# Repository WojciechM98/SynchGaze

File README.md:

# SynchGaze
A project that allows you to control camera movement by moving your head.

## Project assumptions
The project includes two boards SynchGaze Transmiter and SynchGaze Motor Control that communicate with each other via bluetooth.

## SynchGaze Transmiter
Transmiter board has IMU device to collect position, acceleration and rotation data. Every information is preprocessed and send in real time by ESP32 to Motor Control board.
This board should be neatly attached to the user's head.

## SynchGaze Motor Control
Motor Control board recieve preprocessed data from Transmiter and converts it into BLDC motors movement. STM32 works in closed loop gathering data from external IMU device whith is attached in the same place as camera. When new information from Transmiter board is recieved the possition according to external IMU is corrected by sending information about revolutions and acceleration to specific motor controler.

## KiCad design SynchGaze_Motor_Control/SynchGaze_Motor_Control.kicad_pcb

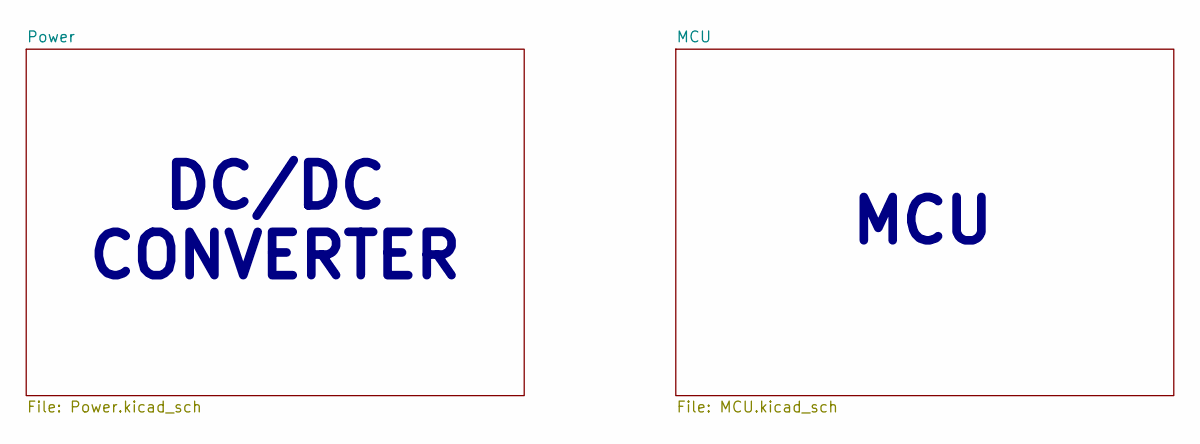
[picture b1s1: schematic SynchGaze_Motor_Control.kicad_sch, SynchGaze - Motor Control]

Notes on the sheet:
DC/DC CONVERTER
MCU

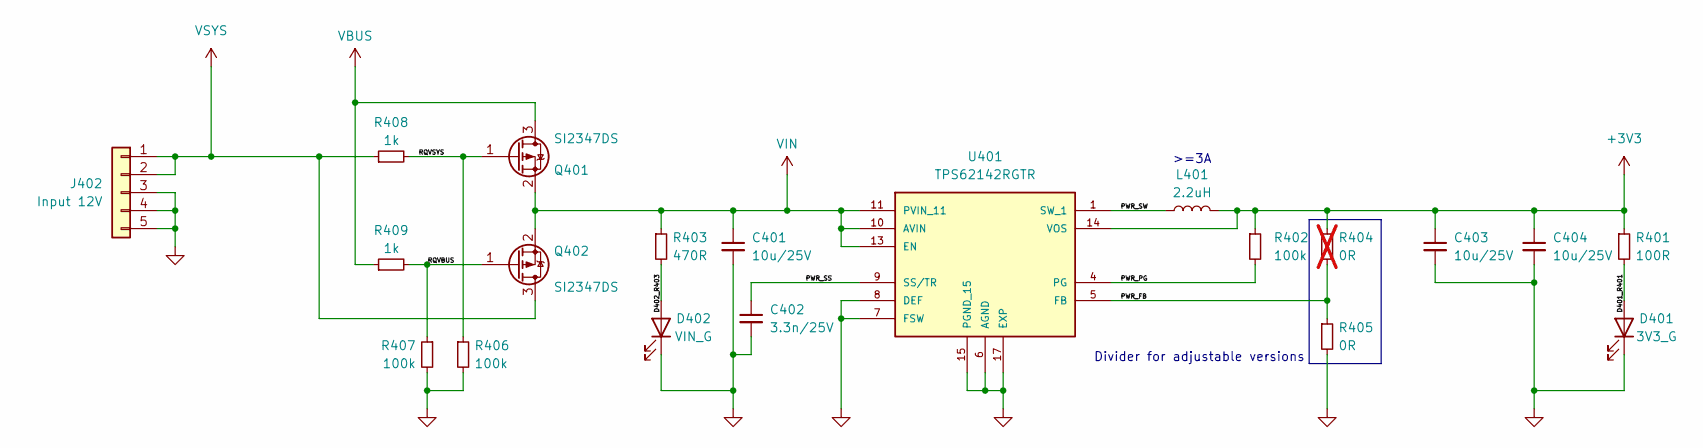
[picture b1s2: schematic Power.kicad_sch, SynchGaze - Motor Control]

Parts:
C401, C403, C404: 10u/25V; C_1206_3216Metric; Manufacturer Part Number CL31B106KAHNFNE
C402: 3.3n/25V; C_0402_1005Metric; Manufacturer Part Number 885012205047
D401: 3V3_G; LED_0603_1608Metric; Manufacturer Part Number 150060GS55040
D402: VIN_G; LED_0603_1608Metric; Manufacturer Part Number 150060GS55040
J402: Input 12V; CONN5_B05B-XASK-1-A_JST
L401: 2.2uH; IHLP1212BZEV2R2MA1; Manufacturer Part Number IHLP1212BZEV2R2MA1
Q401, Q402: SI2347DS; TSOT-23
R401: 100R; R_0402_1005Metric; Manufacturer Part Number RC0402JR-07100RP
R402, R406, R407: 100k; R_0402_1005Metric; Manufacturer Part Number WR04X104 JTL
R403: 470R; R_0402_1005Metric; Manufacturer Part Number RT0402FRE07470RL
R404: 0R; R_0402_1005Metric; Manufacturer Part Number RC0402JR-07100RP; not fitted
R405: 0R; R_0402_1005Metric; Manufacturer Part Number RC0402JR-070RP
R408, R409: 1k; R_0402_1005Metric; Manufacturer Part Number RT0402FRE07470RL
U401: TPS62142RGTR; QFN50P300X300X100-17N_TPS62142RGTR; PARTREV E

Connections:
+3V3: C403.1, C404.1, L401.2, R401.1, R402.1, R404.1, U401.14 (VOS); also elsewhere on the board
/Power/D401_R401: D401.2 (A), R401.2
/Power/D402_R403: D402.2 (A), R403.2
/Power/PWR_FB: R404.2, R405.1, U401.5 (FB)
/Power/PWR_PG: R402.2, U401.4 (PG)
/Power/PWR_SS: C402.1, U401.9 (SS/TR)
/Power/PWR_SW: L401.1, U401.1 (SW_1), U401.2 (SW_2), U401.3 (SW_3)
/Power/RQVBUS: Q402.1 (G), R407.1, R409.2
/Power/RQVSYS: Q401.1 (G), R406.1, R408.2
GND: C401.2, C402.2, C403.2, C404.2, D401.1 (K), D402.1 (K), J402.3, J402.4, J402.5, R405.2, R406.2, R407.2, U401.6 (AGND), U401.7 (FSW), U401.8 (DEF), U401.15 (PGND_15), U401.16 (PGND_16), U401.17 (EXP); also elsewhere on the board
VBUS: Q401.3 (D), R409.1; also elsewhere on the board
VIN: C401.1, Q401.2 (S), Q402.2 (S), R403.1, U401.10 (AVIN), U401.11 (PVIN_11), U401.12 (PVIN_12), U401.13 (EN)
VSYS: J402.1, J402.2, Q402.3 (D), R408.1; also elsewhere on the board

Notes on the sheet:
Divider for adjustable versions
>=3A

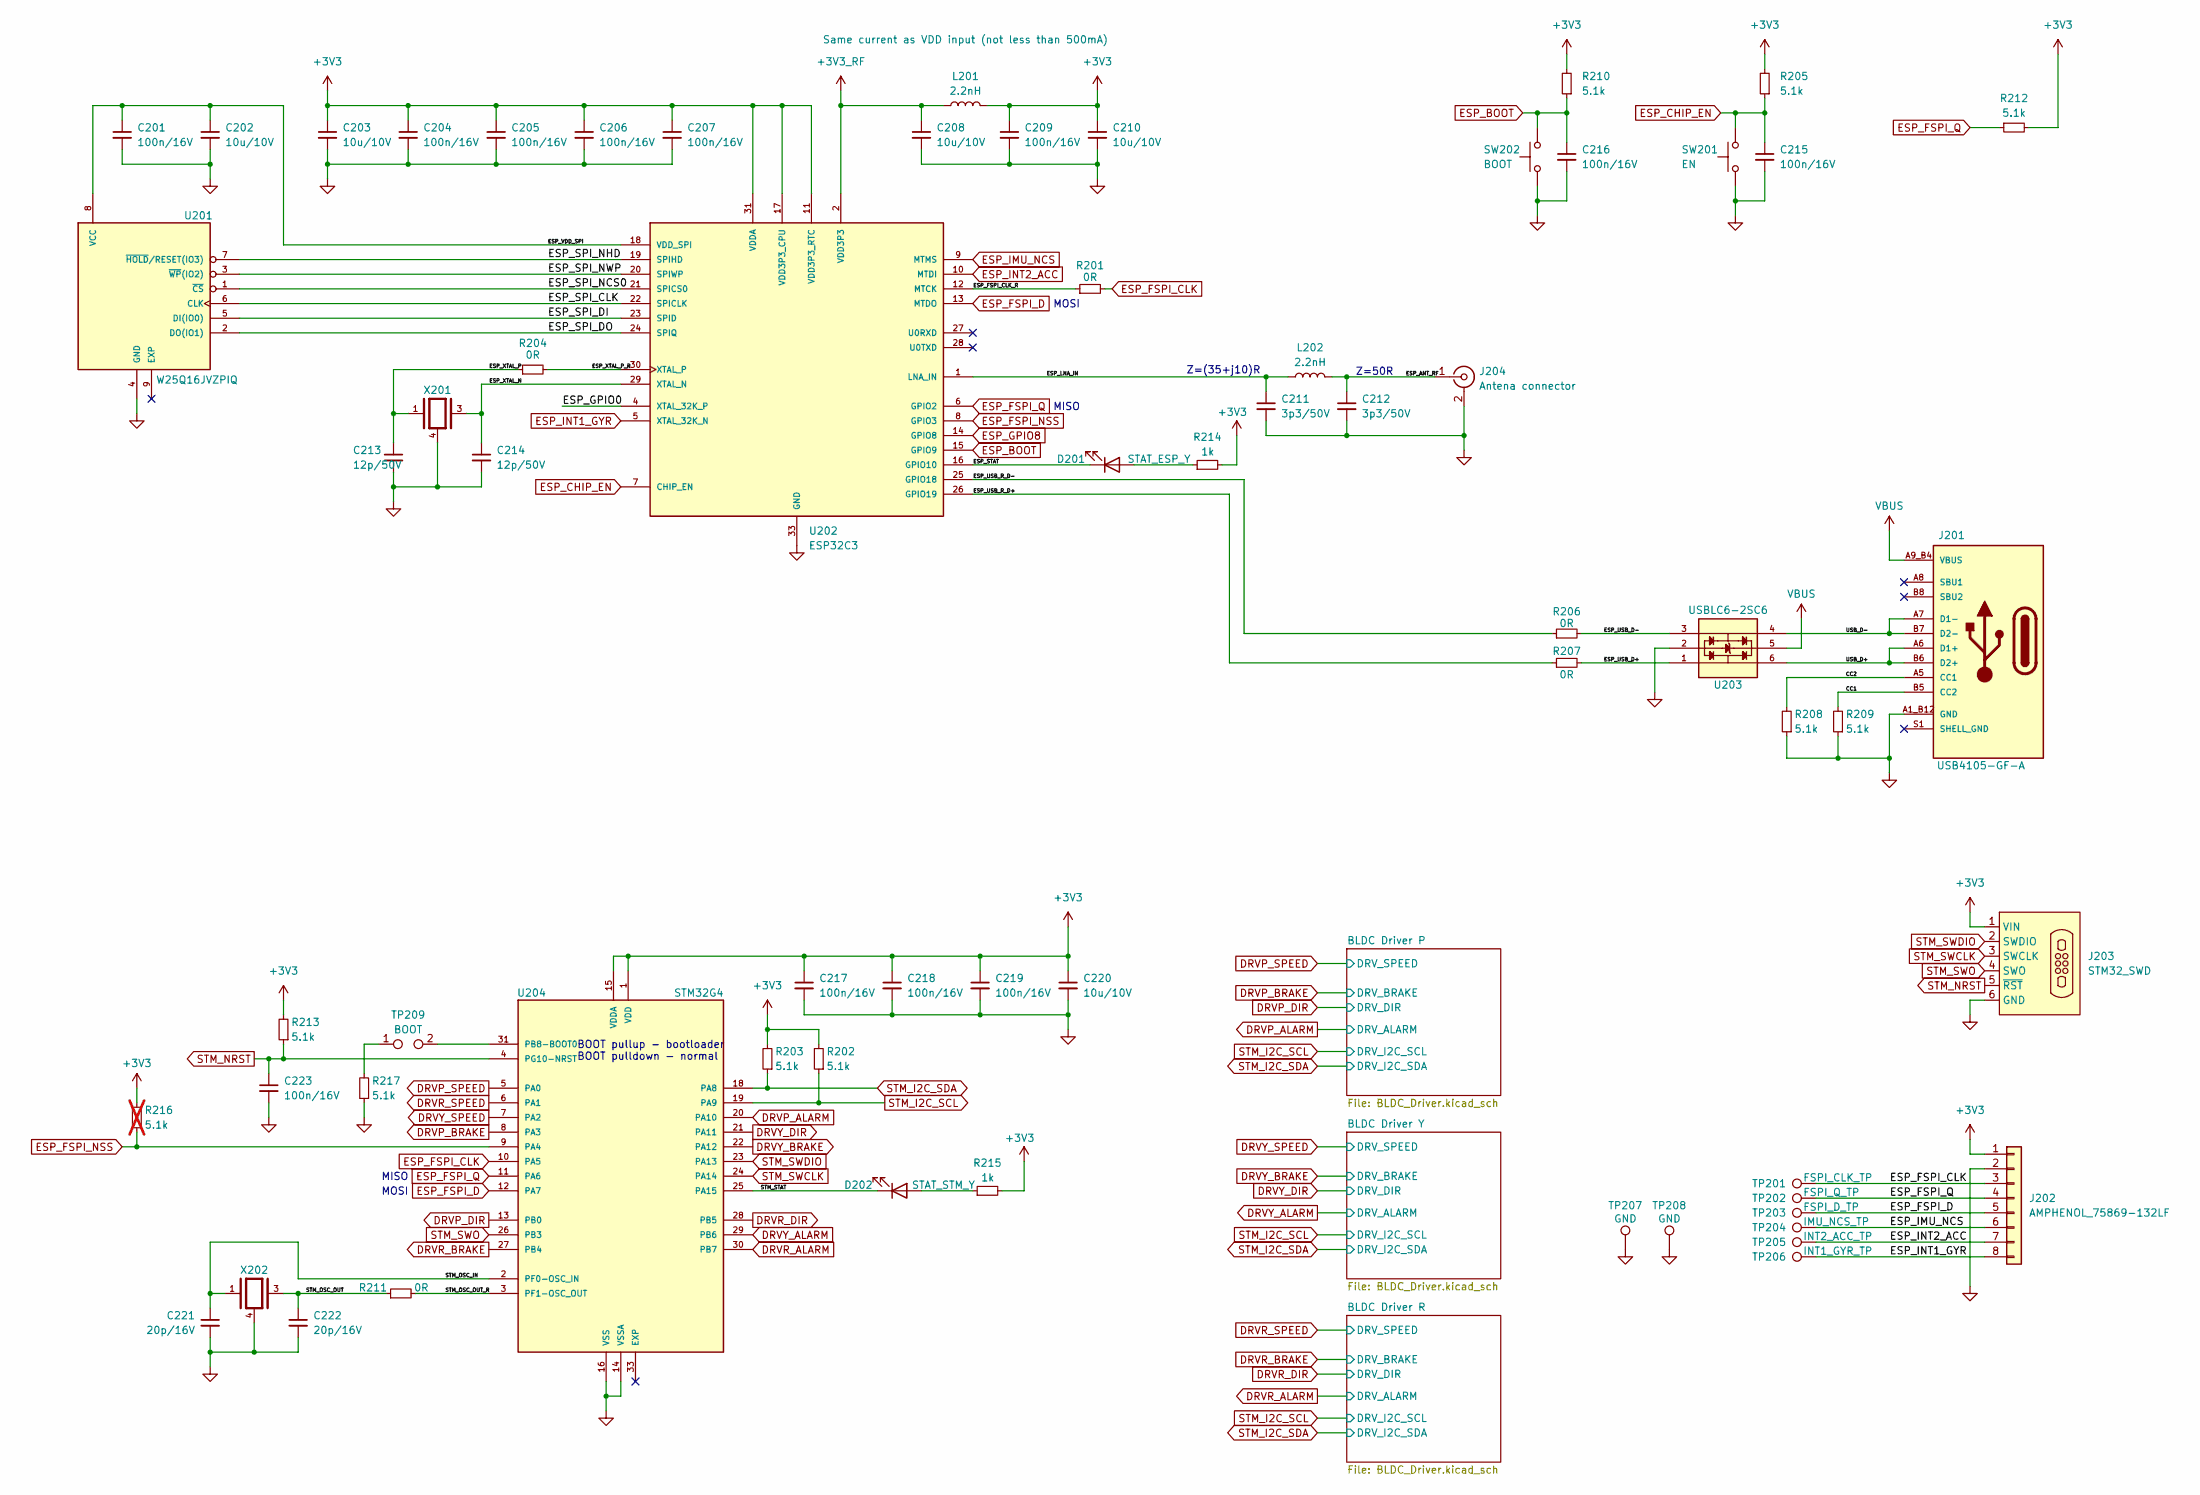
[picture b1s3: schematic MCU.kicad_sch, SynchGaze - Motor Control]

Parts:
C201, C204, C205, C206, C207, C209, C215, C216, C217, C218, C219, C223: 100n/16V; C_0402_1005Metric; Manufacturer Part Number CL05B104JO5NNNC
C202, C203, C208, C210, C220: 10u/10V; C_0402_1005Metric; Manufacturer Part Number GRM155R61A106ME11J
C211, C212: 3p3/50V; C_0402_1005Metric; Manufacturer Part Number 0402N3R3D500CT
C213, C214: 12p/50V; C_0402_1005Metric; Manufacturer Part Number GRM1555C1H120JA01D
C221, C222: 20p/16V; C_0402_1005Metric; Manufacturer Part Number 0402N200J160CT
D201: STAT_ESP_Y; LED_0603_1608Metric; Manufacturer Part Number 150060YS55040
D202: STAT_STM_Y; LED_0603_1608Metric; Manufacturer Part Number 150060YS55040
J201: USB4105-GF-A; GCT_USB4105-GF-A; PARTREV 3
J202: AMPHENOL_75869-132LF; Manufacturer Part Number 0530470810
J203: STM32_SWD; PogoConnector
J204: Antena connector; LINX_CONMHF1-SMD-G-T
L201, L202: 2.2nH; L_0402_1005Metric; Manufacturer Part Number LQG15HN2N2S02D
R201, R204, R206, R207, R211: 0R; R_0402_1005Metric; Manufacturer Part Number RC0402JR-070RP
R202, R203, R205, R208, R209, R210, R212, R213, R217: 5.1k; R_0402_1005Metric; Manufacturer Part Number RT0402FRE075K1L
R214, R215: 1k; R_0402_1005Metric; Manufacturer Part Number RT0402FRE07470RL
R216: 5.1k; R_0402_1005Metric; Manufacturer Part Number RT0402FRE075K1L; not fitted
SW201: EN; SW4_PTS815 SJM 250 SMTR LFS_CNK; Manufacturer Part Number RKB2SJM250SMTR LFS
SW202: BOOT; SW4_PTS815 SJM 250 SMTR LFS_CNK; Manufacturer Part Number RKB2SJM250SMTR LFS
TP201: FSPI_CLK_TP; test_point_SMD_0.5mm
TP202: FSPI_Q_TP; test_point_SMD_0.5mm
TP203: FSPI_D_TP; test_point_SMD_0.5mm
TP204: IMU_NCS_TP; test_point_SMD_0.5mm
TP205: INT2_ACC_TP; test_point_SMD_0.5mm
TP206: INT1_GYR_TP; test_point_SMD_0.5mm
TP207, TP208: GND; test_point_THT 0.7mm
TP209: BOOT; test_point_SMD_two_pad_1mm
U201: W25Q16JVZPIQ; SON127P500X600X80-9N; Manufacturer Part Number W25Q16JVZPIQ
U202: ESP32C3; QFN32_5X5MM_ESP32C3; Manufacturer Part Number ESP32-C3
U203: USBLC6-2SC6; SOT95P280X145-6N; Manufacturer Part Number USBLC6-2SC6
U204: STM32G4; QFN50P500X500X60-33N_STM32G431KBU3; PARTREV 4
X201: XRCGB40M000F4M02R0; OSC_XRCGB40M000F4M02R0; PARTREV N/A
X202: 830108208209; Crystal_SMD_2520-4Pin_2.5x2.0mm; Manufacturer Part Number 830108208209

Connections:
+3V3: C203.1, C204.1, C205.1, C206.1, C207.1, C209.1, C210.1, C217.1, C218.1, C219.1, C220.1, J202.1, J203.1 (VIN), L201.2, R202.2, R203.2, R205.2, R210.2, R212.2, R213.2, R214.2, R215.2, R216.2, U202.11 (VDD3P3_RTC), U202.17 (VDD3P3_CPU), U202.31 (VDDA), U202.32 (VDDA), U204.1 (VDD), U204.15 (VDDA), U204.17 (VDD); also elsewhere on the board
+3V3_RF: C208.1, L201.1, U202.2 (VDD3P3), U202.3 (VDD3P3)
/MCU/CC1: J201.B5 (CC2), R209.2
/MCU/CC2: J201.A5 (CC1), R208.2
/MCU/ESP_ANT_RF: C212.1, J204.1 (In), L202.2
/MCU/ESP_FSPI_CLK_R: R201.1, U202.12 (MTCK)
/MCU/ESP_GPIO0: U202.4 (XTAL_32K_P)
/MCU/ESP_LNA_IN: C211.1, L202.1, U202.1 (LNA_IN)
/MCU/ESP_SPI_CLK: U201.6 (CLK), U202.22 (SPICLK)
/MCU/ESP_SPI_DI: U201.5 (DI(IO0)), U202.23 (SPID)
/MCU/ESP_SPI_DO: U201.2 (DO(IO1)), U202.24 (SPIQ)
/MCU/ESP_SPI_NCS0: U201.1 (~CS), U202.21 (SPICS0)
/MCU/ESP_SPI_NHD: U201.7 (~HOLD/RESET(IO3)), U202.19 (SPIHD)
/MCU/ESP_SPI_NWP: U201.3 (~WP(IO2)), U202.20 (SPIWP)
/MCU/ESP_STAT: D201.1 (K), U202.16 (GPIO10)
/MCU/ESP_USB_D+: R207.2, U203.1
/MCU/ESP_USB_D-: R206.2, U203.3
/MCU/ESP_USB_R_D+: R207.1, U202.26 (GPIO19)
/MCU/ESP_USB_R_D-: R206.1, U202.25 (GPIO18)
/MCU/ESP_VDD_SPI: C201.1, C202.1, U201.8 (VCC), U202.18 (VDD_SPI)
/MCU/ESP_XTAL_N: C214.1, U202.29 (XTAL_N), X201.3
/MCU/ESP_XTAL_P: C213.1, R204.1, X201.1
/MCU/ESP_XTAL_P_R: R204.2, U202.30 (XTAL_P)
/MCU/STM_OSC_IN: C221.1, U204.2 (PF0-OSC_IN), X202.1
/MCU/STM_OSC_OUT: C222.1, R211.1, X202.3
/MCU/STM_OSC_OUT_R: R211.2, U204.3 (PF1-OSC_OUT)
/MCU/STM_STAT: D202.1 (K), U204.25 (PA15)
/MCU/USB_D+: J201.A6 (D1+), J201.B6 (D2+), U203.6
/MCU/USB_D-: J201.A7 (D1-), J201.B7 (D2-), U203.4
DRVP_ALARM: U204.20 (PA10); also elsewhere on the board
DRVP_BRAKE: U204.8 (PA3); also elsewhere on the board
DRVP_DIR: U204.13 (PB0); also elsewhere on the board
DRVP_SPEED: U204.5 (PA0); also elsewhere on the board
DRVR_ALARM: U204.30 (PB7); also elsewhere on the board
DRVR_BRAKE: U204.27 (PB4); also elsewhere on the board
DRVR_DIR: U204.28 (PB5); also elsewhere on the board
DRVR_SPEED: U204.6 (PA1); also elsewhere on the board
DRVY_ALARM: U204.29 (PB6); also elsewhere on the board
DRVY_BRAKE: U204.22 (PA12); also elsewhere on the board
DRVY_DIR: U204.21 (PA11); also elsewhere on the board
DRVY_SPEED: U204.7 (PA2); also elsewhere on the board
ESP_BOOT: C216.1, R210.1, SW202.2, U202.15 (GPIO9)
ESP_CHIP_EN: C215.1, R205.1, SW201.2, U202.7 (CHIP_EN)
ESP_FSPI_CLK: J202.3, R201.2, TP201.1, U204.10 (PA5)
ESP_FSPI_D: J202.5, TP203.1, U202.13 (MTDO), U204.12 (PA7)
ESP_FSPI_NSS: R216.1, U202.8 (GPIO3), U204.9 (PA4)
ESP_FSPI_Q: J202.4, R212.1, TP202.1, U202.6 (GPIO2), U204.11 (PA6)
ESP_GPIO8: U202.14 (GPIO8)
ESP_IMU_NCS: J202.6, TP204.1, U202.9 (MTMS)
ESP_INT1_GYR: J202.8, TP206.1, U202.5 (XTAL_32K_N)
ESP_INT2_ACC: J202.7, TP205.1, U202.10 (MTDI)
GND: C201.2, C202.2, C203.2, C204.2, C205.2, C206.2, C207.2, C208.2, C209.2, C210.2, C211.2, C212.2, C213.2, C214.2, C215.2, C216.2, C217.2, C218.2, C219.2, C220.2, C221.2, C222.2, C223.2, J201.A1_B12 (GND), J201.A12_B1 (GND), J202.2, J203.6 (GND), J204.2 (Ext), R208.1, R209.1, R217.1, SW201.1, SW202.1, TP207.1, TP208.1, U201.4 (GND), U202.33 (GND), U203.2, U204.14 (VSSA), U204.16 (VSS), U204.32 (VSS), X201.2, X201.4, X202.2, X202.4; also elsewhere on the board
unnamed: D201.2 (A), R214.1
unnamed: D202.2 (A), R215.1
unnamed: R217.2, TP209.1
unnamed: TP209.2, U204.31 (PB8-BOOT0)
STM_I2C_SCL: R202.1, U204.19 (PA9); also elsewhere on the board
STM_I2C_SDA: R203.1, U204.18 (PA8); also elsewhere on the board
STM_NRST: C223.1, J203.5 (~RST), R213.1, U204.4 (PG10-NRST)
STM_SWCLK: J203.3 (SWCLK), U204.24 (PA14)
STM_SWDIO: J203.2 (SWDIO), U204.23 (PA13)
STM_SWO: J203.4 (SWO), U204.26 (PB3)
VBUS: J201.A4_B9 (VBUS), J201.A9_B4 (VBUS), U203.5; also elsewhere on the board

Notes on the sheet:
MOSI
Z=(35+j10)R
BOOT pullup - bootloader BOOT pulldown - normal
MISO
Z=50R

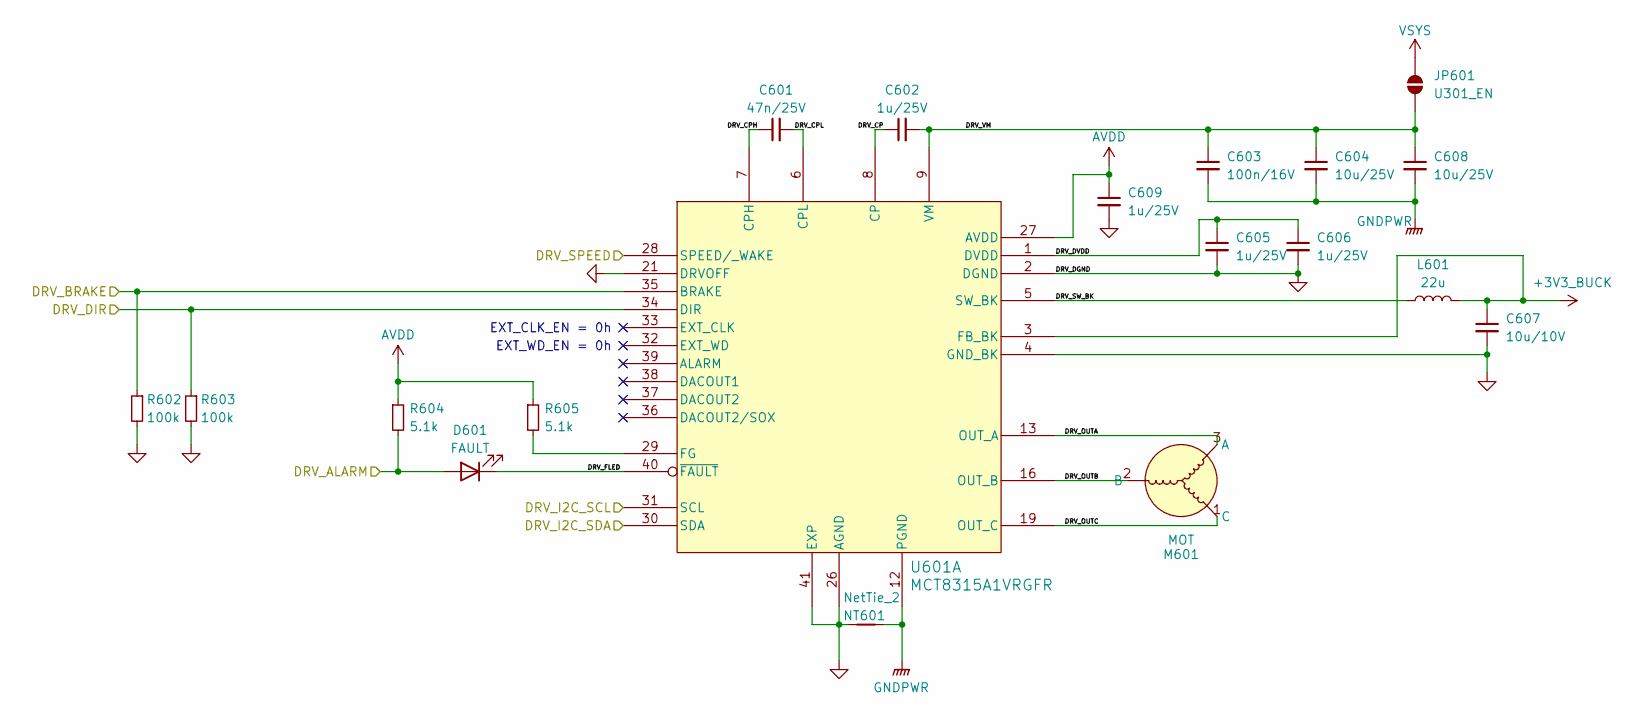
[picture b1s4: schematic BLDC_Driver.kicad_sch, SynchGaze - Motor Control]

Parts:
C601: 47n/25V; C_0402_1005Metric; Manufacturer Part Number GRT155R71E473KE01D
C602, C605, C606, C609: 1u/25V; C_0402_1005Metric; Manufacturer Part Number GRM155R61E105KA12J
C603: 100n/16V; C_0402_1005Metric; Manufacturer Part Number CL05B104JO5NNNC
C604, C608: 10u/25V; C_1206_3216Metric; Manufacturer Part Number CL31B106KAHNFNE
C607: 10u/10V; C_0402_1005Metric; Manufacturer Part Number GRM155R61A106ME11J
D601: FAULT; LED_0603_1608Metric; Manufacturer Part Number SML-D12U1WT86
JP601: U301_EN; SolderJumper-2_P1.3mm_Open_RoundedPad1.0x1.5mm
L601: 22u; L_1210_3225Metric; Manufacturer Part Number CBC3225T220MR
M601: MOT; 15EDGVC-3-5-03P
NT601: NetTie_2; NetTie_2_0.4mm
R602, R603: 100k; R_0402_1005Metric; Manufacturer Part Number WR04X104 JTL
R604, R605: 5.1k; R_0402_1005Metric; Manufacturer Part Number RT0402FRE075K1L
U601: MCT8315A1VRGFR; VQFN40_RGF_TEX_MCT8315A1VRGFR; Manufacturer Part Number MCT8315A1VRGFR

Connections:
+3V3_BUCK: C607.1, L601.2, U601.3 (FB_BK); also elsewhere on the board
/MCU/BLDC Driver R/DRV_CP: C602.1, U601.8 (CP)
/MCU/BLDC Driver R/DRV_CPH: C601.1, U601.7 (CPH)
/MCU/BLDC Driver R/DRV_CPL: C601.2, U601.6 (CPL)
/MCU/BLDC Driver R/DRV_DVDD: C605.1, C606.1, U601.1 (DVDD)
/MCU/BLDC Driver R/DRV_FLED: D601.1 (K), U601.40 (~FAULT)
/MCU/BLDC Driver R/DRV_OUTA: M601.3 (A), U601.13 (OUT_A), U601.14 (OUT_A)
/MCU/BLDC Driver R/DRV_OUTB: M601.2 (B), U601.16 (OUT_B), U601.17 (OUT_B)
/MCU/BLDC Driver R/DRV_OUTC: M601.1 (C), U601.19 (OUT_C), U601.20 (OUT_C)
/MCU/BLDC Driver R/DRV_SW_BK: L601.1, U601.5 (SW_BK)
AVDD: C609.1, R604.1, R605.1, U601.27 (AVDD); also elsewhere on the board
DRVR_ALARM: D601.2 (A), R604.2; also elsewhere on the board
DRVR_BRAKE: R602.1, U601.35 (BRAKE); also elsewhere on the board
DRVR_DIR: R603.1, U601.34 (DIR); also elsewhere on the board
DRVR_SPEED: U601.28 (SPEED/_WAKE); also elsewhere on the board
GND: C605.2, C606.2, C607.2, C609.2, NT601.2, R602.2, R603.2, U601.2 (DGND), U601.4 (GND_BK), U601.21 (DRVOFF), U601.26 (AGND), U601.41 (EXP); also elsewhere on the board
GNDPWR: C603.2, C604.2, C608.2, NT601.1, U601.12 (PGND), U601.15 (PGND), U601.18 (PGND); also elsewhere on the board
unnamed: R605.2, U601.29 (FG)
STM_I2C_SCL: U601.31 (SCL); also elsewhere on the board
STM_I2C_SDA: U601.30 (SDA); also elsewhere on the board
VM: C602.2, C603.1, C604.1, C608.1, JP601.1 (A), U601.9 (VM), U601.10 (VM), U601.11 (VM); also elsewhere on the board
VSYS: JP601.2 (B); also elsewhere on the board

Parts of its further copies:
C301, C501: 47n/25V; C_0402_1005Metric; Manufacturer Part Number GRT155R71E473KE01D
C302, C305, C306, C309, C502, C506, C507, C509: 1u/25V; C_0402_1005Metric; Manufacturer Part Number GRM155R61E105KA12J
C303, C503: 100n/16V; C_0402_1005Metric; Manufacturer Part Number CL05B104JO5NNNC
C304, C308, C504, C505: 10u/25V; C_1206_3216Metric; Manufacturer Part Number CL31B106KAHNFNE
C307, C508: 10u/10V; C_0402_1005Metric; Manufacturer Part Number GRM155R61A106ME11J
D301, D501: FAULT; LED_0603_1608Metric; Manufacturer Part Number SML-D12U1WT86
JP301, JP501: U301_EN; SolderJumper-2_P1.3mm_Open_RoundedPad1.0x1.5mm
L301, L501: 22u; L_1210_3225Metric; Manufacturer Part Number CBC3225T220MR
M301, M501: MOT; 15EDGVC-3-5-03P
NT301, NT501: NetTie_2; NetTie_2_0.4mm
R302, R303, R502, R503: 100k; R_0402_1005Metric; Manufacturer Part Number WR04X104 JTL
R304, R305, R504, R505: 5.1k; R_0402_1005Metric; Manufacturer Part Number RT0402FRE075K1L
U301, U501: MCT8315A1VRGFR; VQFN40_RGF_TEX_MCT8315A1VRGFR; Manufacturer Part Number MCT8315A1VRGFR

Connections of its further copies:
+3V3_BUCK: C307.1, C508.1, L301.2, L501.2, U301.3 (FB_BK), U501.3 (FB_BK); also elsewhere on the board
/MCU/BLDC Driver P/DRV_CP: C502.1, U501.8 (CP)
/MCU/BLDC Driver P/DRV_CPH: C501.1, U501.7 (CPH)
/MCU/BLDC Driver P/DRV_CPL: C501.2, U501.6 (CPL)
/MCU/BLDC Driver P/DRV_DVDD: C506.1, C507.1, U501.1 (DVDD)
/MCU/BLDC Driver P/DRV_FLED: D501.1 (K), U501.40 (~FAULT)
/MCU/BLDC Driver P/DRV_OUTA: M501.3 (A), U501.13 (OUT_A), U501.14 (OUT_A)
/MCU/BLDC Driver P/DRV_OUTB: M501.2 (B), U501.16 (OUT_B), U501.17 (OUT_B)
/MCU/BLDC Driver P/DRV_OUTC: M501.1 (C), U501.19 (OUT_C), U501.20 (OUT_C)
/MCU/BLDC Driver P/DRV_SW_BK: L501.1, U501.5 (SW_BK)
/MCU/BLDC Driver Y/DRV_CP: C302.1, U301.8 (CP)
/MCU/BLDC Driver Y/DRV_CPH: C301.1, U301.7 (CPH)
/MCU/BLDC Driver Y/DRV_CPL: C301.2, U301.6 (CPL)
/MCU/BLDC Driver Y/DRV_DVDD: C305.1, C306.1, U301.1 (DVDD)
/MCU/BLDC Driver Y/DRV_FLED: D301.1 (K), U301.40 (~FAULT)
/MCU/BLDC Driver Y/DRV_OUTA: M301.3 (A), U301.13 (OUT_A), U301.14 (OUT_A)
/MCU/BLDC Driver Y/DRV_OUTB: M301.2 (B), U301.16 (OUT_B), U301.17 (OUT_B)
/MCU/BLDC Driver Y/DRV_OUTC: M301.1 (C), U301.19 (OUT_C), U301.20 (OUT_C)
/MCU/BLDC Driver Y/DRV_SW_BK: L301.1, U301.5 (SW_BK)
AVDD: C309.1, C509.1, R304.1, R305.1, R504.1, R505.1, U301.27 (AVDD), U501.27 (AVDD); also elsewhere on the board
DRVP_ALARM: D501.2 (A), R504.2; also elsewhere on the board
DRVP_BRAKE: R502.1, U501.35 (BRAKE); also elsewhere on the board
DRVP_DIR: R503.1, U501.34 (DIR); also elsewhere on the board
DRVP_SPEED: U501.28 (SPEED/_WAKE); also elsewhere on the board
DRVY_ALARM: D301.2 (A), R304.2; also elsewhere on the board
DRVY_BRAKE: R302.1, U301.35 (BRAKE); also elsewhere on the board
DRVY_DIR: R303.1, U301.34 (DIR); also elsewhere on the board
DRVY_SPEED: U301.28 (SPEED/_WAKE); also elsewhere on the board
GND: C305.2, C306.2, C307.2, C309.2, C506.2, C507.2, C508.2, C509.2, NT301.2, NT501.2, R302.2, R303.2, R502.2, R503.2, U301.2 (DGND), U301.4 (GND_BK), U301.21 (DRVOFF), U301.26 (AGND), U301.41 (EXP), U501.2 (DGND), U501.4 (GND_BK), U501.21 (DRVOFF), U501.26 (AGND), U501.41 (EXP); also elsewhere on the board
GNDPWR: C303.2, C304.2, C308.2, C503.2, C504.2, C505.2, NT301.1, NT501.1, U301.12 (PGND), U301.15 (PGND), U301.18 (PGND), U501.12 (PGND), U501.15 (PGND), U501.18 (PGND); also elsewhere on the board
unnamed: R305.2, U301.29 (FG)
unnamed: R505.2, U501.29 (FG)
STM_I2C_SCL: U301.31 (SCL), U501.31 (SCL); also elsewhere on the board
STM_I2C_SDA: U301.30 (SDA), U501.30 (SDA); also elsewhere on the board
VM: C302.2, C303.1, C304.1, C308.1, C502.2, C503.1, C504.1, C505.1, JP301.1 (A), JP501.1 (A), U301.9 (VM), U301.10 (VM), U301.11 (VM), U501.9 (VM), U501.10 (VM), U501.11 (VM); also elsewhere on the board
VSYS: JP301.2 (B), JP501.2 (B); also elsewhere on the board

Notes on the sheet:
EXT_CLK_EN = 0h
EXT_WD_EN = 0h

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
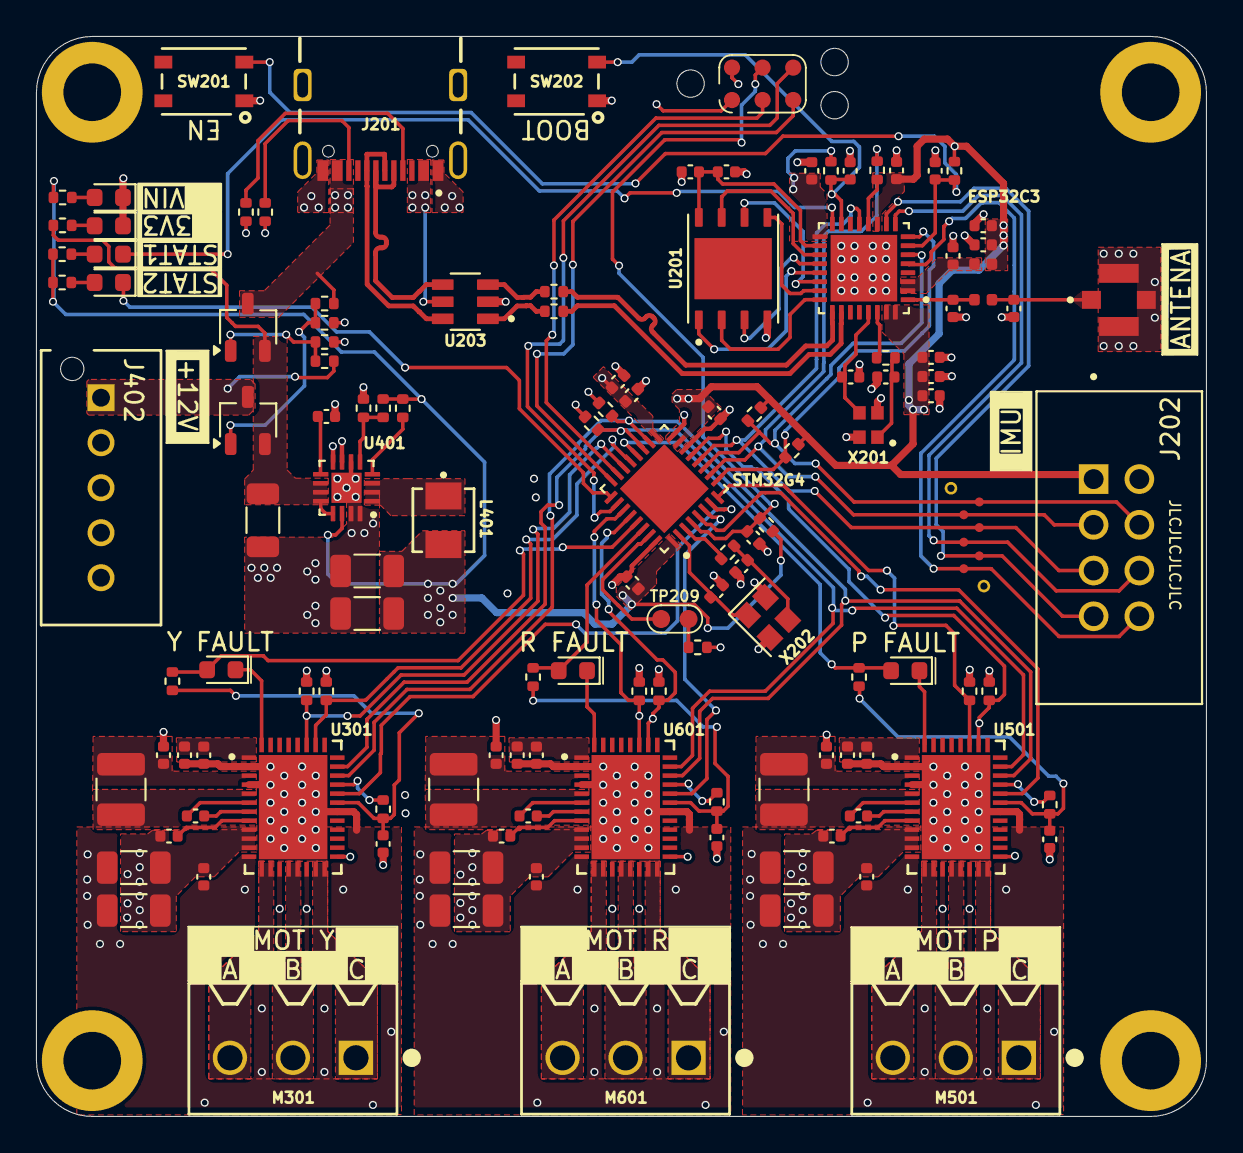
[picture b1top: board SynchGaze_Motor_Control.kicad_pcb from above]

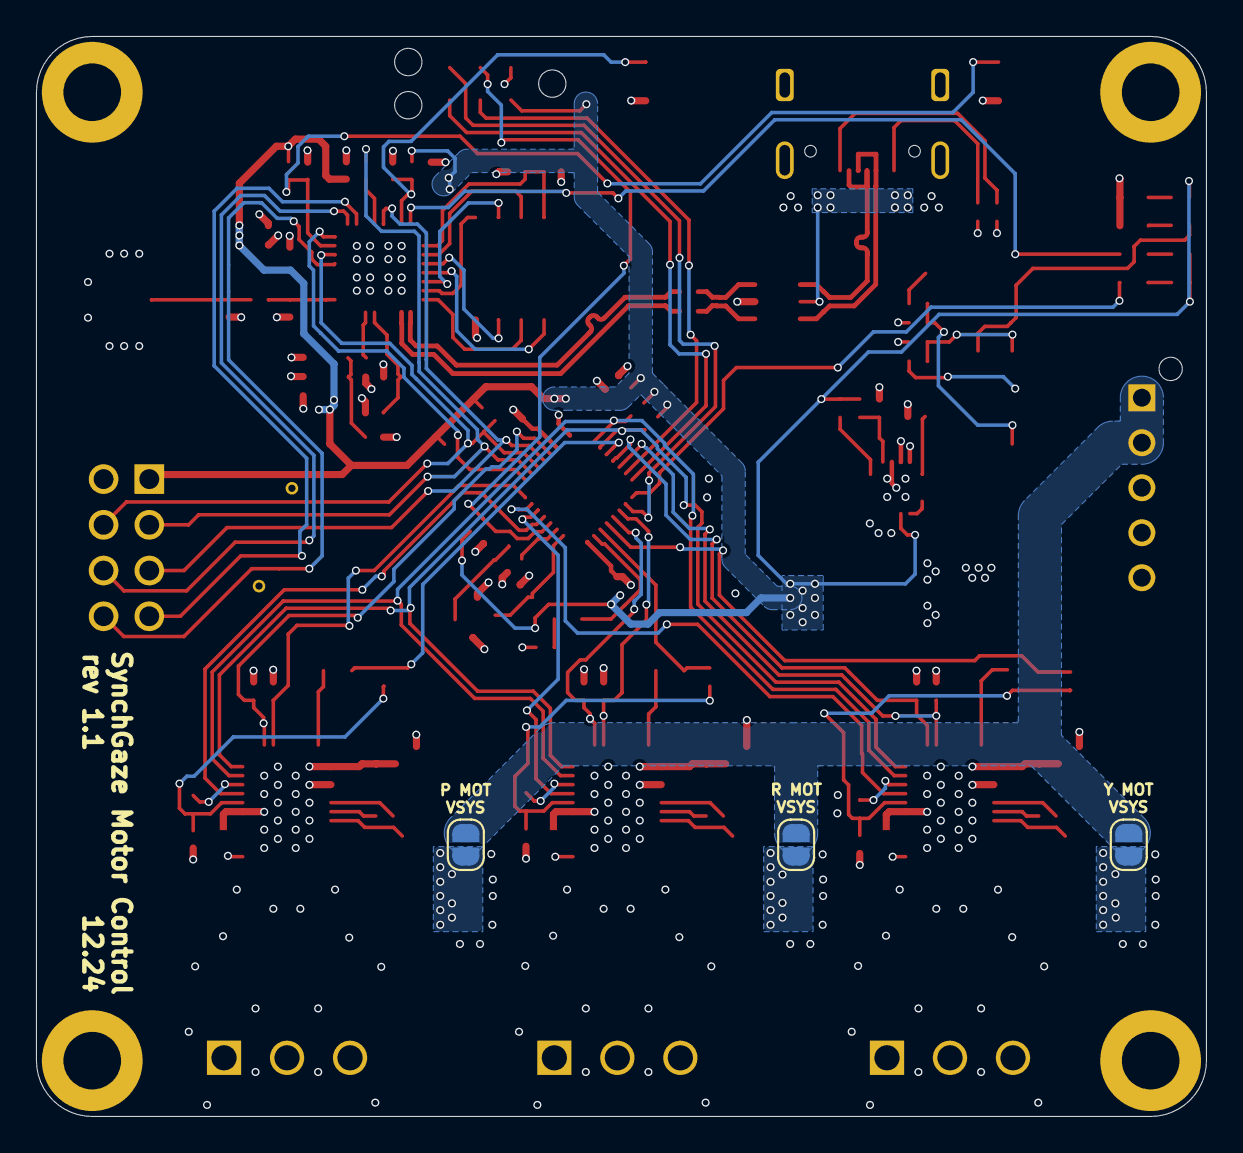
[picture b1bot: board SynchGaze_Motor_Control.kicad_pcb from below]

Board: 4 copper layers, 65.0 x 60.0 mm, 142 parts (3 on the bottom side), 105 nets.

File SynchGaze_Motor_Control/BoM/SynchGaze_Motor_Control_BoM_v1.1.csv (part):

"Qty","Reference","Value","Datasheet","Footprint","Manufacturer","Manufacturer Part Number","Mouser","TME","TME addon"
"15","C201,C204,C205,C206,C207,C209,C215,C216,C217,C218,C219,C223,C303,C503,C603","100n/16V","~","Capacitor_SMD:C_0402_1005Metric","Samsung Electro-Mechanics","CL05B104JO5NNNC","https://www.mouser.pl/ProductDetail/Samsung-Electro-Mechanic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","",""
"8","C202,C203,C208,C210,C220,C307,C508,C607","10u/10V","~","Capacitor_SMD:C_0402_1005Metric","Murata Electronics","GRM155R61A106ME11J","https://www.mouser.pl/ProductDetail/Murata-Electronics/GRM15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","",""
"2","C211,C212","3p3/50V","~","Capacitor_SMD:C_0402_1005Metric","Walsin","0402N3R3D500CT","https://www.mouser.pl/ProductDetail/Walsin/0402N3R3D500CT?qs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","",""
"2","C213,C214","12p/50V","~","Capacitor_SMD:C_0402_1005Metric","Murata Electronics","GRM1555C1H120JA01D","https://www.mouser.pl/ProductDetail/Murata-Electronics/GRM15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","",""
"2","C221,C222","20p/16V","~","Capacitor_SMD:C_0402_1005Metric","Walsin","0402N200J160CT","https://www.mouser.pl/ProductDetail/Walsin/0402N200J160CT?qs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","",""
"3","C301,C501,C601","47n/25V","~","Capacitor_SMD:C_0402_1005Metric","Murata Electronics","GRT155R71E473KE01D","https://www.mouser.pl/ProductDetail/Murata-Electronics/GRT15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","",""
"12","C302,C305,C306,C309,C502,C506,C507,C509,C602,C605,C606,C609","1u/25V","~","Capacitor_SMD:C_0402_1005Metric","Murata Electronics","GRM155R61E105KA12J","https://www.mouser.pl/ProductDetail/Murata-Electronics/GRM15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","",""
"9","C304,C308,C401,C403,C404,C504,C505,C604,C608","10u/25V","~","Capacitor_SMD:C_1206_3216Metric","Samsung Electro-Mechanics","CL31B106KAHNFNE","https://www.mouser.pl/ProductDetail/Samsung-Electro-Mechanic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","",""
"1","C402","3.3n/25V","~","Capacitor_SMD:C_0402_1005Metric","Wurth Elektronik","885012205047","https://www.mouser.pl/ProductDetail/Wurth-Elektronik/8850122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","",""
"1","D201","STAT_ESP_Y","https://www.we-online.com/components/products/datasheet/1500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","LED_SMD:LED_0603_1608Metric","Wurth Elektronik","150060YS55040","https://www.mouser.pl/ProductDetail/Wurth-Elektronik/150060Y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","",""
"1","D202","STAT_STM_Y","https://www.we-online.com/components/products/datasheet/1500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","LED_SMD:LED_0603_1608Metric","Wurth Elektronik","150060YS55040","https://www.mouser.pl/ProductDetail/Wurth-Elektronik/150060Y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","",""
"3","D301,D501,D601","FAULT","~","LED_SMD:LED_0603_1608Metric","ROHM Semiconductor","SML-D12U1WT86","https://www.mouser.pl/ProductDetail/ROHM-Semiconductor/SML-D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","",""
"1","D401","3V3_G","https://www.we-online.com/components/products/datasheet/1500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","LED_SMD:LED_0603_1608Metric","Wurth Elektronik","150060GS55040","https://www.mouser.pl/ProductDetail/Wurth-Elektronik/150060G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","",""
"1","D402","VIN_G","https://www.we-online.com/components/products/datasheet/1500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","LED_SMD:LED_0603_1608Metric","Wurth Elektronik","150060GS55040","https://www.mouser.pl/ProductDetail/Wurth-Elektronik/150060G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","",""
"1","J201","USB4105-GF-A","https://www.mouser.pl/datasheet/2/837/Global_Connector_Techn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","USB4105-GF-A:GCT_USB4105-GF-A","GCT","USB4105-GF-A-120","https://www.mouser.pl/ProductDetail/GCT/USB4105-GF-A-120?qs=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","",""
"1","J202","AMPHENOL_75869-132LF","https://www.tme.eu/Document/f2e550843355180434b4491ce10fcd00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","AMPHENOL_75869-132LF:AMPHENOL_75869-132LF","AMPHENOL","0530470810","","https://www.tme.eu/pl/details/75869-132lf/zlacza-idc/ampheno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",""
"1","J203","STM32_SWD","","PogoPin:PogoConnector","","","","",""
"1","J204","Antena connector","https://www.mouser.pl/datasheet/2/418/9/ENG_DS_conmhf1_smd_g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","CONMHF1-SMD-G-T:LINX_CONMHF1-SMD-G-T","","","https://www.mouser.pl/ProductDetail/TE-Connectivity-Linx-Tec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","",""
"1","J402","Input 12V","https://www.tme.eu/Document/4c7d7d44b355c5ac47b1cea6ab35c76b/XA.pdf","B05B_XASK_1_A_LF__SN_:CONN5_B05B-XASK-1-A_JST","","","","https://www.tme.eu/pl/details/b05b-xask-1/zlacza-sygnalowe-r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",""
"2","L201,L202","2.2nH","~","Inductor_SMD:L_0402_1005Metric","Murata Electronics","LQG15HN2N2S02D","https://www.mouser.pl/ProductDetail/Murata-Electronics/LQG15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","",""
"3","L301,L501,L601","22u","~","Inductor_SMD:L_1210_3225Metric","TAIYO YUDEN"," CBC3225T220MR","https://www.mouser.pl/ProductDetail/TAIYO-YUDEN/CBC3225T220M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","",""
"1","L401","2.2uH","https://www.vishay.com/docs/34536/ihlp-1212bz-a1.pdf","IHLP1212BZEV2R2MA1:IHLP1212BZEV2R2MA1","Vishay"," IHLP1212BZEV2R2MA1","https://www.mouser.pl/ProductDetail/Vishay-Dale/IHLP1212BZEV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","",""
"3","M301,M501,M601","MOT","https://www.tme.eu/Document/83e7173fe653a2d0e44585e87978945b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","15EDGVC-3-5-03P:15EDGVC-3-5-03P","","","","https://www.tme.eu/pl/details/15edgvc-3.5-03p/listwy-zacisko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","https://www.tme.eu/pl/details/15edgk-3.5_3p/listwy-zaciskowe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"
"2","Q401,Q402","SI2347DS","https://www.vishay.com/docs/62827/si2347ds.pdf","Package_TO_SOT_SMD:TSOT-23","","","https://www.mouser.pl/ProductDetail/Vishay-Semiconductors/SI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","",""
"6","R201,R204,R206,R207,R211,R405","0R","~","Resistor_SMD:R_0402_1005Metric","YAGEO","RC0402JR-070RP","https://www.mouser.pl/ProductDetail/YAGEO/RC0402JR-070RP?qs=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","",""
"16","R202,R203,R205,R208,R209,R210,R212,R213,R216,R217,R304,R305,R504,R505,R604,R605","5.1k","~","Resistor_SMD:R_0402_1005Metric","YAGEO","RT0402FRE075K1L","https://www.mouser.pl/ProductDetail/YAGEO/RT0402FRE075K1L?qs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","",""
"4","R214,R215,R408,R409","1k","~","Resistor_SMD:R_0402_1005Metric","YAGEO","RT0402FRE07470RL","https://www.mouser.pl/ProductDetail/YAGEO/RT0402FRE07470RL?q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","",""
"9","R302,R303,R402,R406,R407,R502,R503,R602,R603","100k","~","Resistor_SMD:R_0402_1005Metric","Walsin","WR04X104 JTL","https://www.mouser.pl/ProductDetail/Walsin/WR04X104-JTL?qs=1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","",""
"1","R401","100R","~","Resistor_SMD:R_0402_1005Metric","YAGEO","RC0402JR-07100RP","https://www.mouser.pl/ProductDetail/YAGEO/RC0402JR-07100RP?q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","",""
"1","R403","470R","~","Resistor_SMD:R_0402_1005Metric","YAGEO","RT0402FRE07470RL","https://www.mouser.pl/ProductDetail/YAGEO/RT0402FRE07470RL?q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","",""
"1","SW201","EN","~","RKB2SJM250SMTR_LFS:SW4_PTS815 SJM 250 SMTR LFS_CNK","C&K"," RKB2SJM250SMTR LFS","https://www.mouser.pl/ProductDetail/CK/RKB2SJM250SMTR-LFS?qs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","",""
"1","SW202","BOOT","~","RKB2SJM250SMTR_LFS:SW4_PTS815 SJM 250 SMTR LFS_CNK","C&K"," RKB2SJM250SMTR LFS","https://www.mouser.pl/ProductDetail/CK/RKB2SJM250SMTR-LFS?qs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","",""
"1","TP201","FSPI_CLK_TP","~","TEST_POINT:test_point_SMD_0.5mm","","","","",""
"1","TP202","FSPI_Q_TP","~","TEST_POINT:test_point_SMD_0.5mm","","","","",""
"1","TP203","FSPI_D_TP","~","TEST_POINT:test_point_SMD_0.5mm","","","","",""
"1","TP204","IMU_NCS_TP","~","TEST_POINT:test_point_SMD_0.5mm","","","","",""
"1","TP205","INT2_ACC_TP","~","TEST_POINT:test_point_SMD_0.5mm","","","","",""
"1","TP206","INT1_GYR_TP","~","TEST_POINT:test_point_SMD_0.5mm","","","","",""
"2","TP207,TP208","GND","~","TEST_POINT:test_point_THT 0.7mm","","","","",""
"1","TP209","BOOT","~","TEST_POINT:test_point_SMD_two_pad_1mm","","","","",""
"1","U201","W25Q16JVZPIQ","","W25Q16JVZPIQ:SON127P500X600X80-9N","Winbond","W25Q16JVZPIQ","https://www.mouser.pl/ProductDetail/Winbond/W25Q16JVZPIQ?qs=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","",""
"1","U202","ESP32C3","","ESP32C3:QFN32_5X5MM_ESP32C3","Espressif Systems","ESP32-C3","https://www.mouser.pl/ProductDetail/Espressif-Systems/ESP32-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","",""
"1","U203","USBLC6-2SC6","","USBLC6-2SC6:SOT95P280X145-6N","STMicroelectronics","USBLC6-2SC6","https://www.mouser.pl/ProductDetail/STMicroelectronics/USBLC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","",""
"1","U204","STM32G4","https://www.mouser.pl/datasheet/2/389/stm32g431c6-1600866.pdf","STM32G431KBU3:QFN50P500X500X60-33N_STM32G431KBU3","STMicroelectronics","STM32G431KBU6","https://www.mouser.pl/ProductDetail/STMicroelectronics/STM32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","",""
"3","U301,U501,U601","MCT8315A1VRGFR","https://www.ti.com/lit/ds/symlink/mct8315a.pdf?ts=1721889725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","MCT8315A1VRGFR:VQFN40_RGF_TEX_MCT8315A1VRGFR","Texas Instruments","MCT8315A1VRGFR","https://www.mouser.pl/ProductDetail/Texas-Instruments/MCT831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","",""
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
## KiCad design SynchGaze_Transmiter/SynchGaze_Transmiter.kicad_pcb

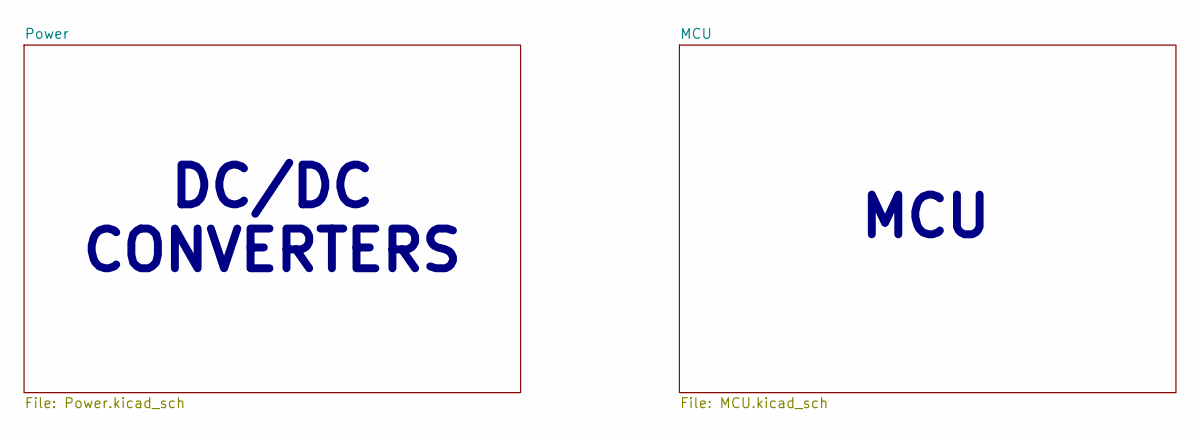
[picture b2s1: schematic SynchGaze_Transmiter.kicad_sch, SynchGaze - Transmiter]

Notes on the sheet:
MCU
DC/DC CONVERTERS
